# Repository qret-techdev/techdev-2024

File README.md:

# techdev-2024

GitHub for QRET's 2023 - 2024 Tech Dev Project!

This will be the platform to save and work off of all code, including both the processing and hardware components.

Each contributor will have their own branch, where they can work off of their projects. This allows everyone to have their own space while being able to check up on what others are up to.

Please reach out to Teighin Nordholt on Slack if you have any questions about using GitHub or how it works for our subteam!

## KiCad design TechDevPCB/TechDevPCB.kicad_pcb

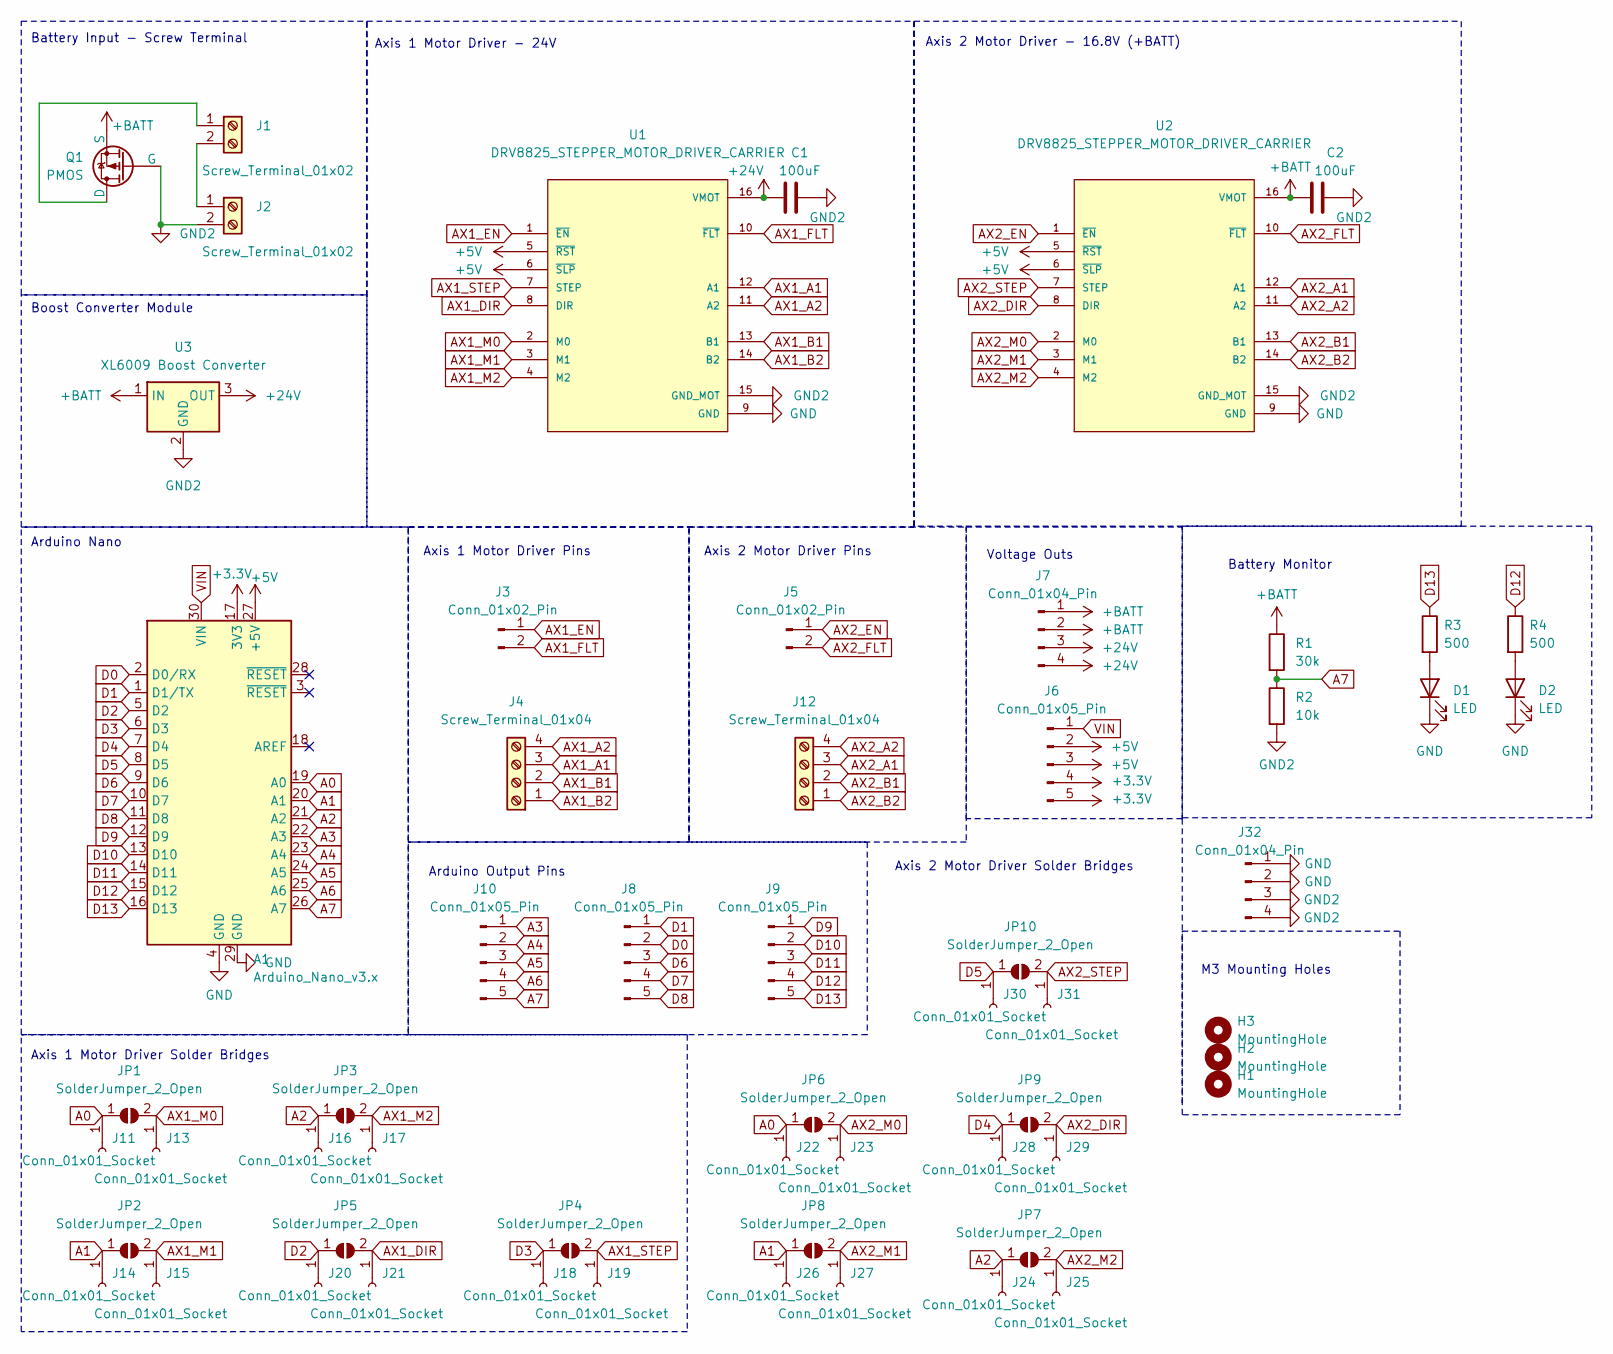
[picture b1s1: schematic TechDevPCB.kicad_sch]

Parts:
A1: Arduino_Nano_v3.x; Arduino_Nano
C1, C2: 100uF; C_Radial_D5.0mm_H5.0mm_P2.00mm
D1, D2: LED; LED_Rectangular_W3.0mm_H2.0mm
H1, H2, H3: MountingHole; MountingHole_3.2mm_M3_DIN965
J1, J2: Screw_Terminal_01x02; TerminalBlock_bornier-2_P5.08mm
J3, J5: Conn_01x02_Pin; PinHeader_1x02_P2.54mm_Vertical
J4, J12: Screw_Terminal_01x04; TerminalBlock_bornier-4_P5.08mm
J6, J8, J9, J10: Conn_01x05_Pin; PinHeader_1x05_P2.54mm_Vertical
J7, J32: Conn_01x04_Pin; PinHeader_1x04_P2.54mm_Vertical
J11, J13, J14, J15, J16, J17, J18, J19, J20, J21, J22, J23, J24, J25, J26, J27, J28, J29, J30, J31: Conn_01x01_Socket; PinHeader_1x01_P2.54mm_Vertical
JP1, JP2, JP3, JP4, JP5, JP6, JP7, JP8, JP9, JP10: SolderJumper_2_Open; SolderJumper-2_P1.3mm_Open_Pad1.0x1.5mm
Q1: PMOS; TO-251-3-1EP_Horizontal_TabDown
R1: 30k; R_Axial_DIN0207_L6.3mm_D2.5mm_P10.16mm_Horizontal
R2: 10k; R_Axial_DIN0207_L6.3mm_D2.5mm_P10.16mm_Horizontal
R3, R4: 500; R_Axial_DIN0207_L6.3mm_D2.5mm_P10.16mm_Horizontal
U1, U2: DRV8825_STEPPER_MOTOR_DRIVER_CARRIER; IC_DRV8825_STEPPER_MOTOR_DRIVER_CARRIER
U3: XL6009 Boost Converter

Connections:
+3.3V: A1.17 (3V3), J6.4, J6.5
+5V: A1.27 (+5V), J6.2, J6.3, U1.5 (~RST), U1.6 (~SLP), U2.5 (~RST), U2.6 (~SLP)
+24V: C1.1, J7.3, J7.4, U1.16 (VMOT), U3.3 (OUT)
+BATT: C2.1, J7.1, J7.2, Q1.3 (S), R1.1, U2.16 (VMOT), U3.1 (IN)
A0: A1.19 (A0), J11.1, J22.1, JP1.1 (A), JP6.1 (A)
A1: A1.20 (A1), J14.1, J26.1, JP2.1 (A), JP8.1 (A)
A2: A1.21 (A2), J16.1, J24.1, JP3.1 (A), JP7.1 (A)
A3: A1.22 (A3), J10.1
A4: A1.23 (A4), J10.2
A5: A1.24 (A5), J10.3
A6: A1.25 (A6), J10.4
A7: A1.26 (A7), J10.5, R1.2, R2.1
AX1_A1: J4.3, U1.12 (A1)
AX1_A2: J4.4, U1.11 (A2)
AX1_B1: J4.2, U1.13 (B1)
AX1_B2: J4.1, U1.14 (B2)
AX1_DIR: J21.1, JP5.2 (B), U1.8 (DIR)
AX1_EN: J3.1, U1.1 (~EN)
AX1_FLT: J3.2, U1.10 (~FLT)
AX1_M0: J13.1, JP1.2 (B), U1.2 (M0)
AX1_M1: J15.1, JP2.2 (B), U1.3 (M1)
AX1_M2: J17.1, JP3.2 (B), U1.4 (M2)
AX1_STEP: J19.1, JP4.2 (B), U1.7 (STEP)
AX2_A1: J12.3, U2.12 (A1)
AX2_A2: J12.4, U2.11 (A2)
AX2_B1: J12.2, U2.13 (B1)
AX2_B2: J12.1, U2.14 (B2)
AX2_DIR: J29.1, JP9.2 (B), U2.8 (DIR)
AX2_EN: J5.1, U2.1 (~EN)
AX2_FLT: J5.2, U2.10 (~FLT)
AX2_M0: J23.1, JP6.2 (B), U2.2 (M0)
AX2_M1: J27.1, JP8.2 (B), U2.3 (M1)
AX2_M2: J25.1, JP7.2 (B), U2.4 (M2)
AX2_STEP: J31.1, JP10.2 (B), U2.7 (STEP)
D0: A1.2 (D0/RX), J8.2
D1: A1.1 (D1/TX), J8.1
D2: A1.5 (D2), J20.1, JP5.1 (A)
D3: A1.6 (D3), J18.1, JP4.1 (A)
D4: A1.7 (D4), J28.1, JP9.1 (A)
D5: A1.8 (D5), J30.1, JP10.1 (A)
D6: A1.9 (D6), J8.3
D7: A1.10 (D7), J8.4
D8: A1.11 (D8), J8.5
D9: A1.12 (D9), J9.1
D10: A1.13 (D10), J9.2
D11: A1.14 (D11), J9.3
D12: A1.15 (D12), J9.4, R4.1
D13: A1.16 (D13), J9.5, R3.1
GND: A1.4 (GND), A1.29 (GND), D1.1 (K), D2.1 (K), J32.1, J32.2, U1.9 (GND), U2.9 (GND)
GND2: C1.2, C2.2, J2.2, J32.3, J32.4, Q1.2 (G), R2.2, U1.15 (GND_MOT), U2.15 (GND_MOT), U3.2 (GND)
unnamed: D1.2 (A), R3.2
unnamed: D2.2 (A), R4.2
unnamed: J1.1, Q1.1 (D)
unnamed: J1.2, J2.1
VIN: A1.30 (VIN), J6.1

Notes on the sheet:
Boost Converter Module
Axis 2 Motor Driver Pins
Axis 1 Motor Driver Pins
Axis 1 Motor Driver Solder Bridges
Arduino Nano
Battery Input - Screw Terminal
Axis 1 Motor Driver - 24V
Arduino Output Pins
Battery Monitor
M3 Mounting Holes
Axis 2 Motor Driver - 16.8V (+BATT)
Axis 2 Motor Driver Solder Bridges
Voltage Outs

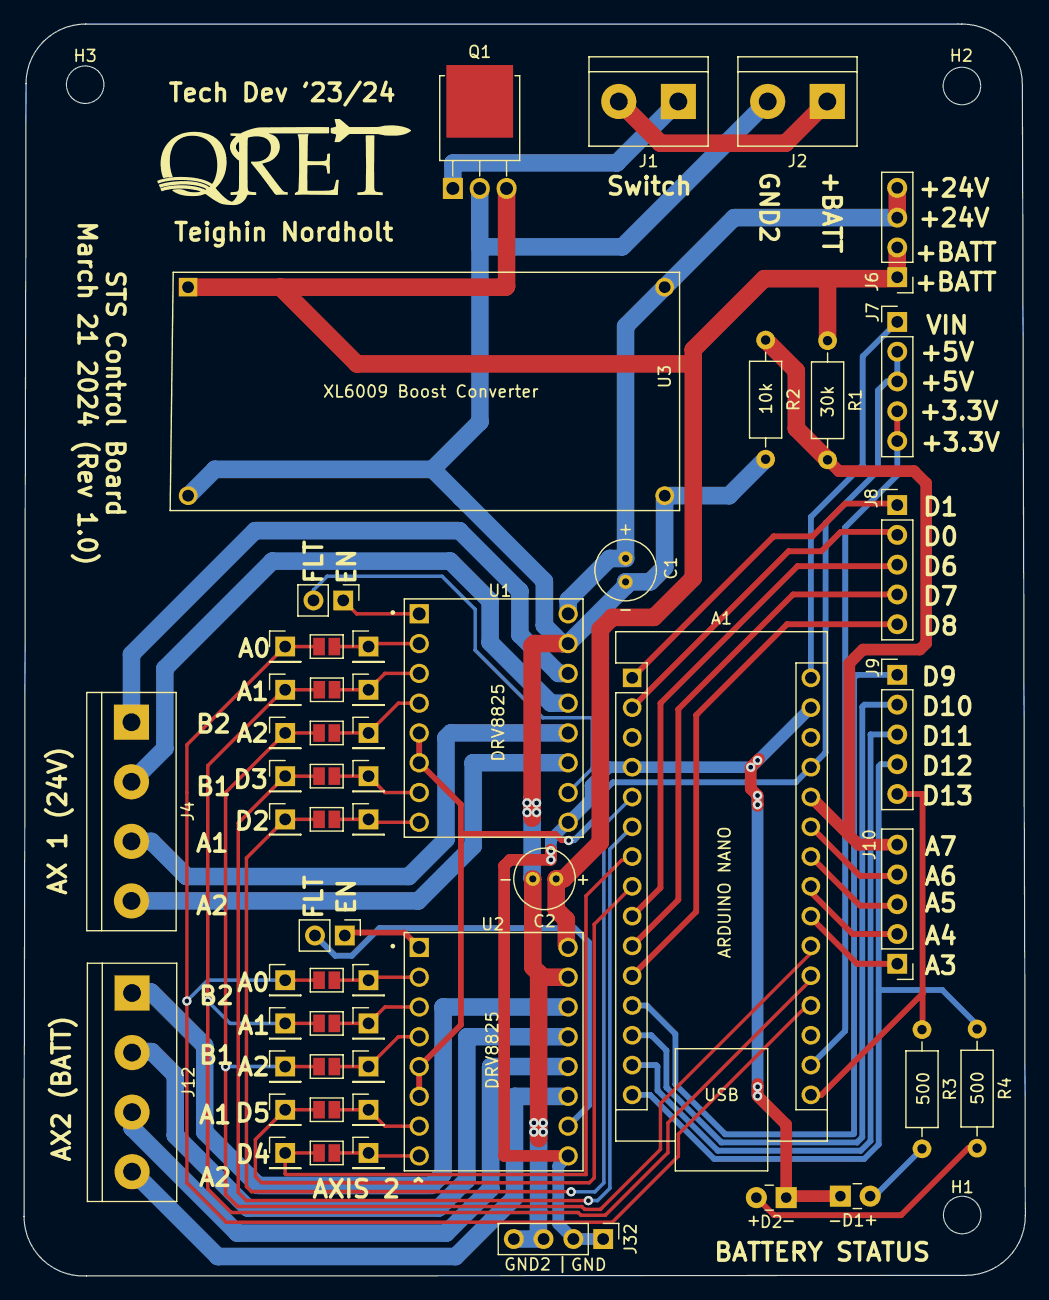
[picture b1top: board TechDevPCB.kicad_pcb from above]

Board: 2 copper layers, 85.4 x 106.8 mm, 58 parts (0 on the bottom side), 55 nets.

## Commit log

2023-10-21 Add files via upload
    Initial upload of preliminary tests
2023-11-12 Trying out PID library
2023-11-13 Image Splitter Test
2023-11-18 uploading preliminary detect and train code
2023-11-20 Created using Colaboratory
2023-11-20 yolov5 with model1
2023-11-20 create model and data
2023-11-20 added test_data
2023-11-20 Image Splitting Test
2023-11-21 Testing Machine Learning Model w/ i7-12700 and 3060
2023-11-21 uploaded videos tested on Model1
2024-01-17 added tests data
2024-01-17 updated folder names
2024-01-17 added training file with graphs
2024-01-23 added drawing of first draft of software architecture
2024-01-23 changed gitignore
2024-01-23 change gitgnore
2024-02-06 Prelim laser tracking for upcoming test
2024-02-15 implementing basic untuned pid for preliminary tests
2024-02-15 increased serial speed
2024-02-16 after test!
2024-02-24 Small changes and updated PID constants
2024-03-04 Code flow chart
2024-03-06 added yolov7 code
2024-03-06 Update code diagram
2024-03-06 removed unecesarry files from merge
2024-03-06 turned into a function for calling in detect.py
2024-03-06 added pid_track function
2024-03-06 fixed function finish tasks
2024-03-06 move file to yolov7 folder
2024-03-07 prelim code for 2d test
2024-03-08 working on yolov8 version
2024-03-08 fixed issues in yolov7 version
2024-03-08 deleted unecesarry images
2024-03-09 added print center cords
2024-03-09 added video for testing and model wieghts
2024-03-09 testing yolov8 tracking
2024-03-09 updated names
2024-03-09 added print center statement
2024-03-09 for checking camera status
2024-03-09 commented out code not in use
2024-03-09 added openAI api key
2024-03-09 update before first 2 axis test
2024-03-09 sucessfull attempt using CPU for inference
2024-03-09 made two version CPU and GPU
2024-03-09 updated tracking to include PID
2024-03-09 updated model
2024-03-09 updated for use a GPU comp
2024-03-09 update after sat test
2024-03-09 change center to 240, 320
2024-03-09 fixed the center to 0,0
2024-03-16 initial testing on CUDA machine
2024-03-16 Prelim PCB
2024-03-16 PCB Updates
2024-03-17 Created board
2024-03-18 live updates testing
2024-03-18 first testing edits
2024-03-18 added cpu capability
2024-03-22 added more constants for ease of testing
2024-03-23 updated from saturday's testing
2024-03-31 removed uneccesary yolov7 files
2024-03-31 working on combining PySimpleGUI with tracking code
2024-04-24 testing pid
2024-04-24 modified tristan just for testin
2024-04-24 just for testing
2024-04-24 updated for random shit
2024-04-25 Adjusted PID y proportional value. Fixed batery indicator
2024-04-25 updated .json
2024-05-25 Added new test file to predict rocket location and account for delay
2024-05-26 organized popup and regular code to specific folders for testing an future iterations
2024-05-26 renamed folder to identify the old cv version
2024-05-26 made a SERIAL mode, removed CUDA mode, and trying to add output video
    SERIAL mode is for testing without adding comments, CUDA mode is not needed, and output video is testin still not working.
2024-06-08 added check for total processing time of the code
2024-06-13 Slowed down control to make it slightly more bearable
2024-06-13 added second order prediction
2024-06-14 untested fix for video capture corruption
2024-06-14 added auto calc for initial motor speed
2024-06-20 added pid when switching state to prevent integral buildup
2024-07-01 beginning update to support GUI input and output,
    specifically allowing for change of PID inputs through GUI
2024-07-01 move check_cam.py
2024-07-01 fixed pidy calculation
    was not using the correct value to compute acceleration
2024-07-01 starting kalman predict
2024-07-01 fixed pidy calculation
    was not using filter y location
2024-07-03 added confidence masking to process_frame
2024-07-03 added confidence masking to process_frame()
2024-07-03 trying fix for mov avg when toggling state
2024-07-03 working similation of a 2d efk kalman filter.
    not tested
2024-07-03 moved weights to specific folder
2024-07-03 fixed video output,
    saves to output_video/output_date_time
2024-07-03 fixed output video,
    file saves to output_video/output_date_time
2024-07-03 removed CUDA constant
2024-07-03 using opencv for inference
2024-07-03 uncommited because not needed
2024-07-06 new tracking file with kalman filtering and prediction
2024-07-06 clean up comments and shortened lines used
2024-07-06 removed unnecessary files from when merging from tristan.
2024-07-06 updated location of weights file.
2024-07-11 tracking version which uses pysimplegui to make a gui app
2024-07-11 abstracted the kalman filter calculation
2024-07-11 abstraccted the kalman filter caculation
2024-07-11 added SERIAL constant
2024-07-11 modified script to enable testing
2024-07-11 models trained for testing on short yellow and black rocket
2024-07-11 updated kalman filter
2024-07-11 Update .gitignore for mp4s
2024-07-12 testing
2024-07-12 removed negative, correct y pid consts
2024-07-13 Add File for Config Parameters
2024-07-13 Add Kalman Filter library
2024-07-13 Add Serial Communication class
2024-07-13 Moved Files
2024-07-13 Add Configure Param file
2024-07-13 Add Serial Class
2024-07-13 Add util.py for support function
2024-07-13 Remove old cv version
    no longer needed updated version availble
2024-07-13 Add Ignore PyCache File
2024-07-13 Object tracking library
    - inits all objects and variables
    - inits Kp, Ki, Kd values to ones specified in params.xlsx
2024-07-13 entended Kalman filter library
2024-07-13 Add File for PID params
    - holds x and y kp, ki, and kd
2024-07-13 Add main
    - calls all instanciates all objects
    - performs keyboard event handling
2024-07-13 relocated weights file for OOP tracking version
2024-07-13 Add Ignore PyCache files
2024-07-13 Updated initial tracking speed logic to include speed X
2024-07-13 Update Kalman filter update logic
    - no longer acept input when rocket is not being traked
    - 0,0 is ideally not acheivable unless rocket is lost
2024-07-13 Add test print for comparing filtered cordinates
2024-07-13 added confidence threshold to config
2024-07-13 Add Confidence Thresh and Rocket Tracked %
2024-07-13 Add Frame Counting occurs at state 1
2024-07-13 Add Print for Frame count of # of bounding boxes
2024-07-19 latest yolov10 model and conda env yml
2024-07-20 Uploaded latest yolov10 model, onnx testing script, and input image is padded now
2024-07-20 Added padding to input img and reversed kalman updating only when rocket is visible
2024-07-24 added makedir
2024-07-24 pulled out const t_delay
2024-07-24 removed padding, fixed tristan's fuckup
2024-07-24 updated params
2024-07-24 updated PID consts with most successful before changing to OOP
2024-07-29 re-organized branch focusing just on yolov10 and OOP tracking
2024-07-29 focusing on yolov10
2024-07-29 removed check if model stopped tracking
2024-07-29 removed loop within process_frame, Now chooses most confidence result
2024-07-29 added makedir for video output
2024-07-29 Fixed pid tuning load, added accel preview before state 1, additional testing addition
2024-07-29 updated params to newest from testing branch
2024-07-29 fixed loading of yolov10 weights
2024-07-29 updated to include correct serial library
2024-08-02 reversed X frame rize back to 480
2024-08-03 Fixed conda yml enviroment
2024-08-04 Removed class name in bounding box
    - causes errors with onnx inference
2024-08-04 Add curent best yolov10b onnx model
2024-08-05 Fixed x frame size causeing video failure
2024-08-05 Fixed video recording failure
2024-08-05 onnx benchmarking results
2024-08-06 reverted to ignoring mp4s
2024-08-07 refactored process_frame()
    - removed uncessary cls varaible
2024-08-11 cleaning up sunflow tracking system
2024-08-11 cleaning up tracking system
    - renamed directory for clarity
    - removed all unecessary files
2024-08-11 Added preliminary qt gui project
2024-08-11 Added helper functions and serial class for comm with microcontroller
2024-08-11 Added kalman filter library for filtering x and y centers
2024-08-11 Added singleOjectTracker class - processes frames and provides current velocities x and y in degrees/s - generates missed objects based on last known loc, vel, and accel
2024-08-11 Added main script - holds state machine - provides debugging outputs. - Added Boost mode for prelaunch setup
2024-08-11 holds all configuration parameters for object tracking and micro controller comm
2024-08-11 Removed unused directory
2024-08-11 Fixed naming issue realted to tracker class
2024-08-11 Performed various clean up tasks
    - supported output velocity as integer
    - cleaned up main debugging outputs
2024-08-12 Cleaned up tracker.py and added rolling avg
    - weighted rolling avg vel now implemented
    - clean up initilization functions
    - removed unecessary varaibles in process_center
2024-08-12 Added v8s model interation 242 for testing
2024-08-12 removed redundant parameters
2024-08-12 updated gigignore and added conda environment.yml
2024-08-12 Refactor and optimize tracker codebase
    - Simplified KalmanFilterManager: Improved naming, removed redundancy, and optimized matrix initialization.
    - Modularized main.py: Extracted keypress handling and speed djustments into separate functions.
    - Enhanced tracker.py: Applied correct type casting, streamlined initialization, and improved process efficiency.
    - Updated params.csv: Adjusted settings to align with refactored logic.
2024-08-12 added new model to params and cleaned up velocity prediction
2024-08-13 commit it all shitty branch
2024-08-13 fixes made durring testing
2024-08-16 Cleaned up main
    - moved serial to backend
    - various clean up
2024-08-16 Added pytorch model
2024-08-16 Refactored object tracker
    - reduced relyance on shared varaibles
    - seperated process center into 2 func
    - serial com now in tracker class
    - converted back to using ultralytics
2024-08-16 Added onnx model
2024-08-16 cleaned up branch
    - removed unused files after rebase
2024-08-18 comp updates
